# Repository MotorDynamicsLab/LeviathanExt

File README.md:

# Leviathan Extension Board

The Leviathan Extension Board is a plug and play PCB that expands the feature set of the original Leviathan controller board. It adds: 

- 2x Integrated TMC5160 stepper drivers. 
- 2x Fan ports with flyback protection, 12V/24V selectable voltage, and tachometer inputs. 
- 2x Thermistor ports with 2k2 ohm pullup resistors. 
- 1x Piezo Buzzer

## Electrical Specifications

| Parameter                 | Symbol             | Min | Typ | Max | Unit | Comments                                      |
| ------------------------- | ------------------ | --- | --- | --- | ---- | --------------------------------------------- |
| HV Stepper Supply Voltage | V<sub>HV</sub>     | 24  | 48  | 55  | V    | Supply voltage for the HV stepper drivers     |
| Fan Current               | I<sub>fan</sub>    |     |     | 0.5 | A    | Current rating per fan channel                |
| HV Stepper Current        | I<sub>hv_mot</sub> |     |     | 3   | A    | Current rating of each TMC5160 stepper driver |

## Creating a Custom Extension PCB

Did you ever want to create your own custom extension board? We have a [template KiCad project](https://github.com/MotorDynamicsLab/Leviathan-Ext-Template) to help get you started.

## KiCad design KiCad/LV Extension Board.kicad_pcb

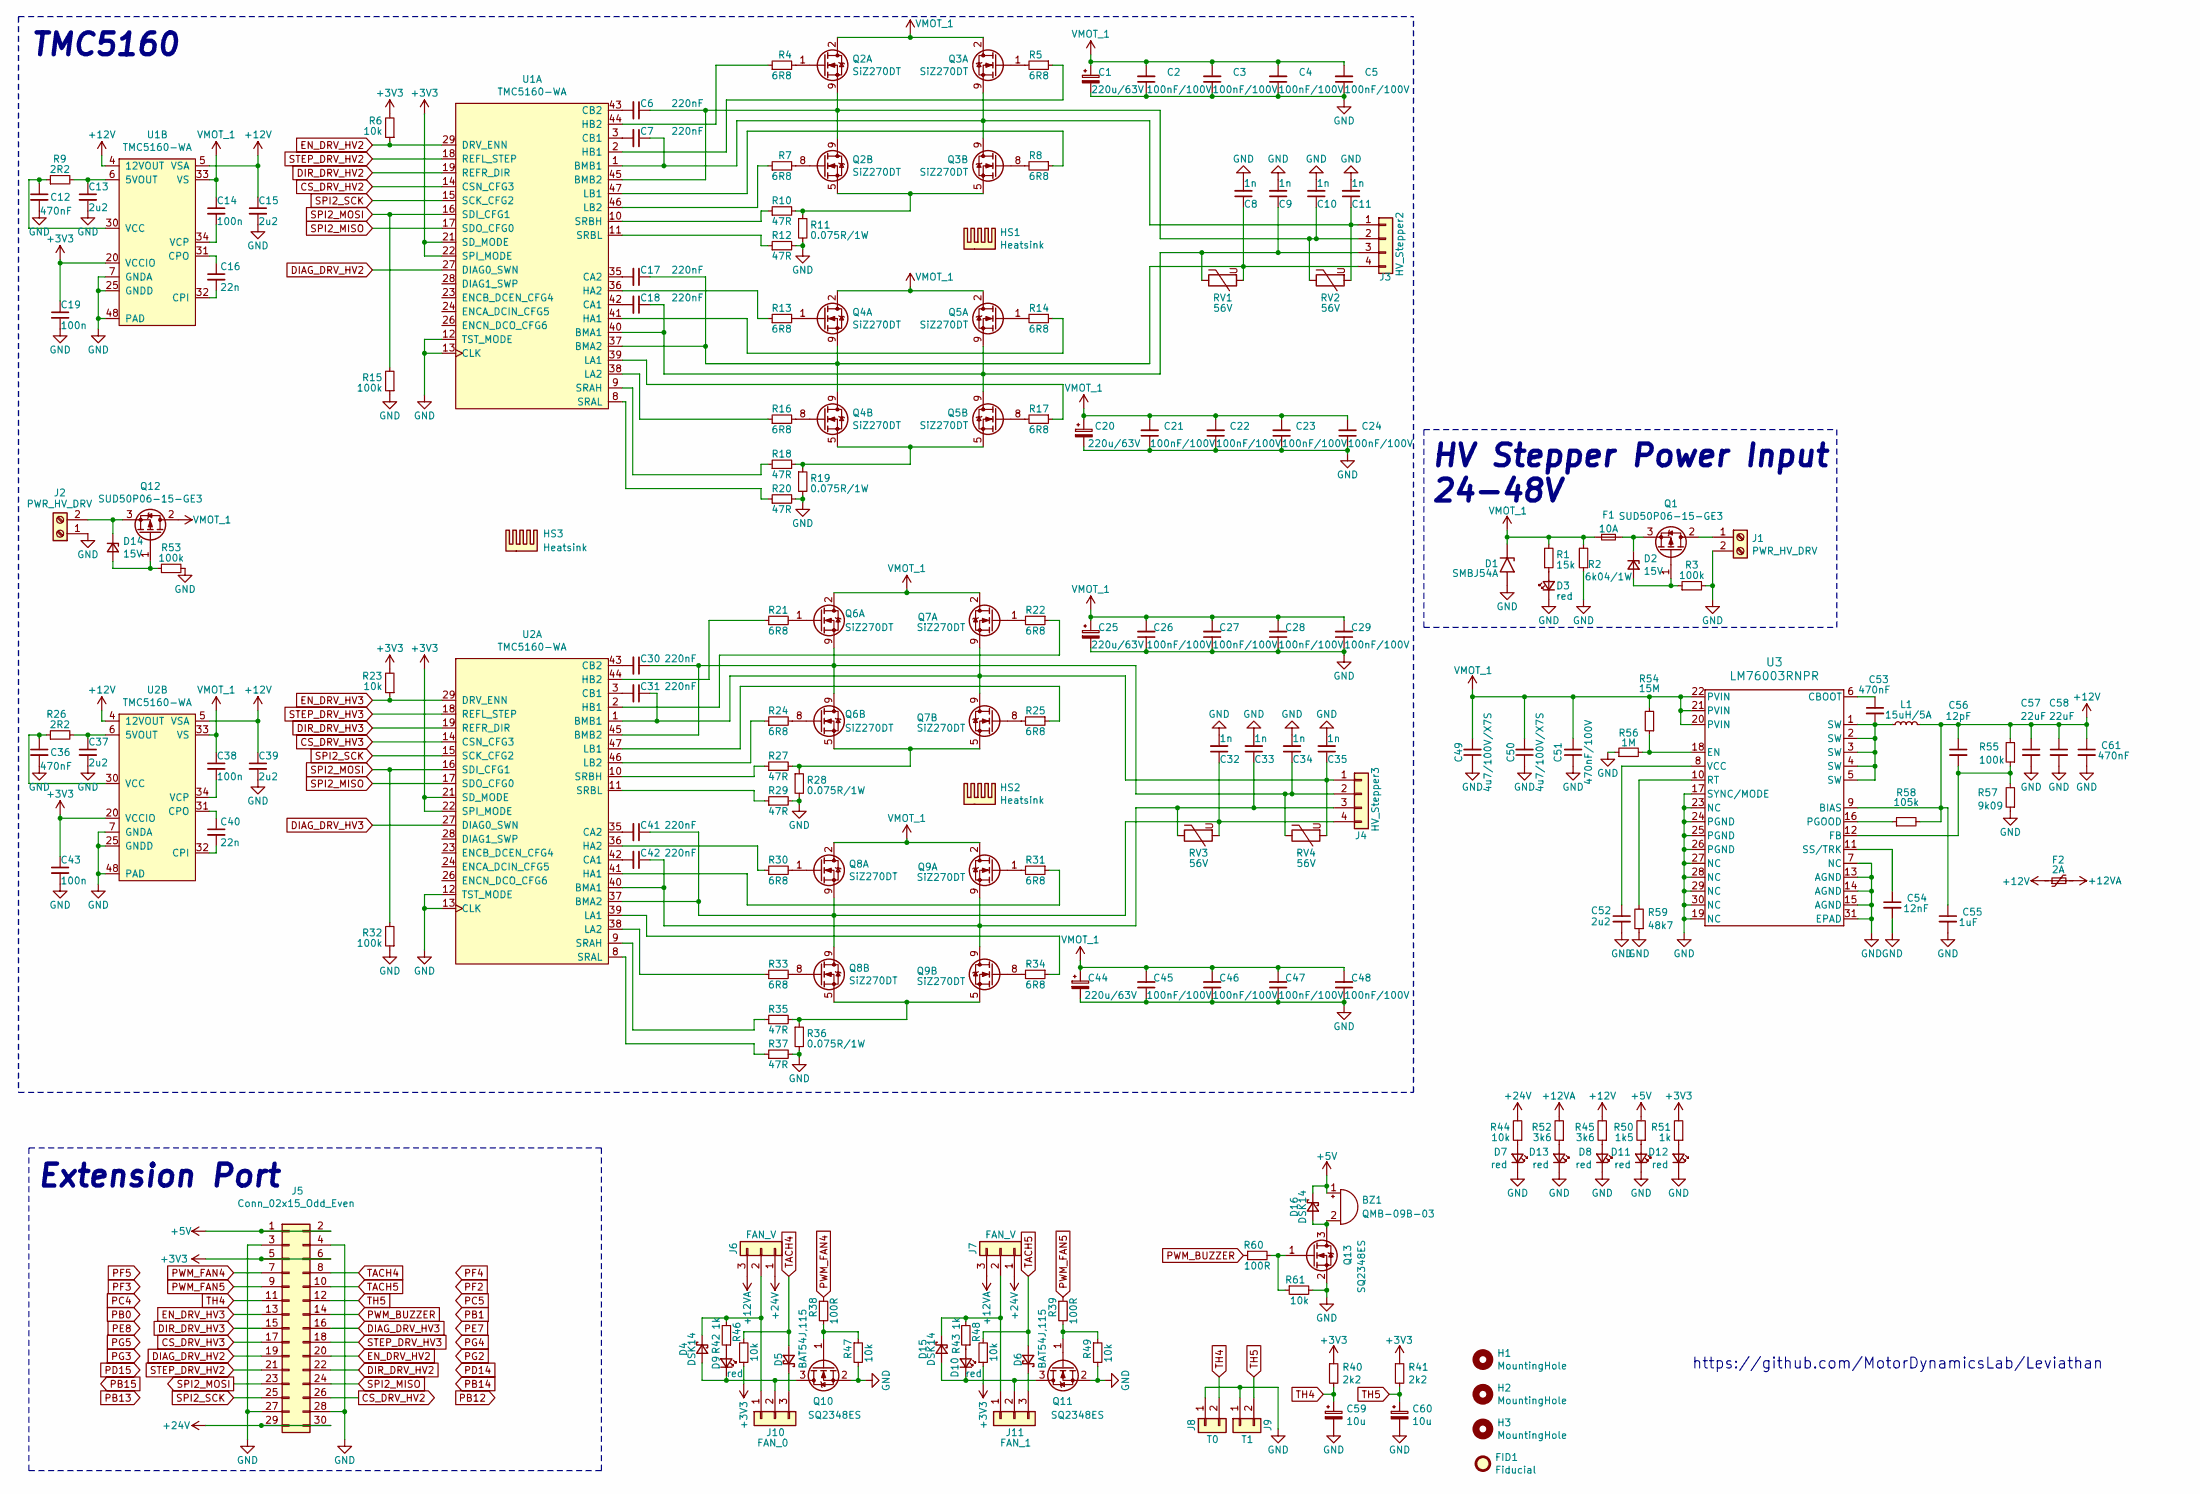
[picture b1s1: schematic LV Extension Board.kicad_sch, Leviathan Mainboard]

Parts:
BZ1: QMB-09B-03; MagneticBuzzer_PUI_AT-0927-TT-6-R; LCSC C96256
C1, C20, C25, C44: 220u/63V; CP_Radial_D10.0mm_P5.00mm; LCSC C442941
C2, C3, C4, C5, C21, C22, C23, C24, C26, C27, C28, C29, C45, C46, C47, C48: 100nF/100V; C_0603_1608Metric; LCSC C88219
C6, C7, C17, C18, C30, C31, C41, C42: 220nF; C_0603_1608Metric; LCSC C2174190
C8, C9, C10, C11, C32, C33, C34, C35: 1n; C_0603_1608Metric; MFG# 0603B102K101CT; LCSC C77438
C12, C36: 470nF; C_0402_1005Metric; LCSC C961501
C13, C15, C37, C39: 2u2; C_0603_1608Metric; LCSC C99228
C14: 100n; C_0603_1608Metric; LCSC# C116838
C16, C40: 22n; C_0603_1608Metric; LCSC C161234
C19, C43: 100n; C_0402_1005Metric; MFG# C83054; LCSC C83054
C38: 100n; C_0603_1608Metric; LCSC C116838
C49, C50: 4u7/100V/X7S; C_1206_3216Metric; LCSC C237304
C51: 470nF/100V; C_0805_2012Metric; LCSC C97926
C52: 2u2; C_0402_1005Metric; LCSC C2999759
C53, C61: 470nF; C_0402_1005Metric; LCSC C437527
C54: 12nF; C_0402_1005Metric; LCSC C113785
C55: 1uF; C_0402_1005Metric; LCSC C1518208
C56: 12pF; C_0402_1005Metric; LCSC C1547
C57, C58: 22uF; C_1206_3216Metric; LCSC C909845
C59, C60: 10u; CP_EIA-3216-18_Kemet-A; MFG# TC212A106M010B; LCSC# C124849
D1: SMBJ54A; D_SMB; LCSC C353352
D2, D14: 15V; D_SOD-123; LCSC C177014
D3, D7, D8, D9, D10, D11, D12, D13: red; LED_0603_1608Metric; LCSC C434419
D4, D15, D16: DSK14; D_SOD-123F; LCSC C37049
D5, D6: BAT54J,115; D_SOD-323_HandSoldering; LCSC C130415
F1: 10A; Fuseholder_Littelfuse_Nano2_154x; LCSC C206921
F2: 2A; Fuse_0805_2012Metric; LCSC C910824
FID1: Fiducial; Fiducial_1.5mm_Mask3mm
H1, H2, H3: MountingHole; MountingHole_3.2mm_M3_Pad_TopBottom
HS1, HS2: Heatsink; Heatsink_Fischer_ICK_PGA_20x20x10
HS3: Heatsink; M2_Heatsink_55x22x3
J1, J2: PWR_HV_DRV; TerminalBlock_Phoenix_MKDS-1,5-2_1x02_P5.00mm_Horizontal
J3: HV_Stepper2; JST_XH_B4B-XH-A_1x04_P2.50mm_Vertical; LCSC C566013
J4: HV_Stepper3; JST_XH_B4B-XH-A_1x04_P2.50mm_Vertical; LCSC C566013
J5: Conn_02x15_Odd_Even; PinHeader_2x15_P2.54mm_Horizontal
J6, J7: FAN_V; PinHeader_1x03_P2.54mm_Vertical; LCSC C429954
J8: T0; JST_XH_B2B-XH-A_1x02_P2.50mm_Vertical; LCSC C161869
J9: T1; JST_XH_B2B-XH-A_1x02_P2.50mm_Vertical; LCSC C161869
J10: FAN_0; JST_XH_B3B-XH-A_1x03_P2.50mm_Vertical; LCSC C565985
J11: FAN_1; JST_XH_B3B-XH-A_1x03_P2.50mm_Vertical; LCSC C565985
L1: 15uH/5A; L_Chilisin_BMRB00060650; LCSC C2847544
Q1, Q12: SUD50P06-15-GE3; TO-252-2; LCSC C141584
Q2, Q3, Q4, Q5: SiZ270DT; Vishay_PowerPair_3x3S; LCSC C17341509
Q6, Q7, Q8, Q9: SiZ270DT; Vishay_PowerPair_3x3S
Q10, Q11, Q13: SQ2348ES; SOT-23; LCSC C7463653
R1: 15k; R_0603_1608Metric; LCSC C73802
R2: 6k04/1W; R_2512_6332Metric; LCSC C421527
R3, R53: 100k; R_0603_1608Metric; LCSC C14675
R4, R5, R7, R8, R13, R14, R16, R17, R21, R22, R24, R25, R30, R31, R33, R34: 6R8; R_0402_1005Metric; LCSC C227211
R6, R23: 10k; R_0402_1005Metric; LCSC C384294
R9, R26: 2R2; R_0402_1005Metric; LCSC C327251
R10, R12, R18, R20, R27, R29, R35, R37: 47R; R_0402_1005Metric; LCSC C144756
R11, R19, R28, R36: 0.075R/1W; R_2512_6332Metric; LCSC C705611
R15, R32: 100k; R_0402_1005Metric; LCSC C132374
R38, R39, R60: 100R; R_0603_1608Metric; LCSC C327825
R40, R41: 2k2; R_0603_1608Metric; LCSC C445630
R42, R43, R51: 1k; R_0603_1608Metric; LCSC C14676
R44: 10k; R_0603_1608Metric; LCSC# C384294
R45, R52: 3k6; R_0603_1608Metric; LCSC C103578
R46, R47, R48, R49, R61: 10k; R_0603_1608Metric; LCSC C384294
R50: 1k5; R_0603_1608Metric; LCSC C22843
R54: 15M; R_0402_1005Metric; LCSC C7422144
R55: 100k; R_0402_1005Metric; LCSC C60491
R56: 1M; R_0402_1005Metric; LCSC C26083
R57: 9k09; R_0402_1005Metric; LCSC C11549
R58: 105k; R_0402_1005Metric; LCSC C171671
R59: 48k7; R_0402_1005Metric; LCSC C103068
RV1, RV2, RV3, RV4: 56V; R_1206_3216Metric; LCSC C2935553
U1, U2: TMC5160-WA; QFN-56-1EP_8x8mm_P0.5mm_EP6.25x6.25mm_ThermalVias_TMC; LCSC C1161714
U3: LM76003RNPR; Texas_RNP30; LCSC C470958

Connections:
+3V3: C19.1, C43.1, J5.5, J5.6, R6.2, R23.2, R40.1, R41.1, R46.1, R48.1, R51.2, U1.20 (VCCIO), U1.21 (SD_MODE), U1.22 (SPI_MODE), U2.20 (VCCIO), U2.21 (SD_MODE), U2.22 (SPI_MODE)
+5V: BZ1.1 (+), D16.1 (K), J5.1, J5.2, R50.2
+12V: C15.1, C39.1, C55.1, C56.1, C57.1, C58.1, C61.1, F2.1, L1.2, R45.2, R55.2, R58.2, U1.4 (12VOUT), U1.5 (VSA), U2.4 (12VOUT), U2.5 (VSA), U3.9 (BIAS)
+12VA: F2.2, J6.3, J7.3, R52.2
+24V: J5.29, J5.30, J6.1, J7.1, R44.2
CS_DRV_HV2: J5.26, U1.14 (CSN_CFG3)
CS_DRV_HV3: J5.17, U2.14 (CSN_CFG3)
DIAG_DRV_HV2: J5.19, U1.27 (DIAG0_SWN)
DIAG_DRV_HV3: J5.16, U2.27 (DIAG0_SWN)
DIR_DRV_HV2: J5.22, U1.19 (REFR_DIR)
DIR_DRV_HV3: J5.15, U2.19 (REFR_DIR)
EN_DRV_HV2: J5.20, R6.1, U1.29 (DRV_ENN)
EN_DRV_HV3: J5.13, R23.1, U2.29 (DRV_ENN)
GND: C1.2, C2.1, C3.1, C4.1, C5.1, C8.2, C9.2, C10.2, C11.2, C12.2, C13.2, C15.2, C19.2, C20.2, C21.1, C22.1, C23.1, C24.1, C25.2, C26.1, C27.1, C28.1, C29.1, C32.2, C33.2, C34.2, C35.2, C36.2, C37.2, C39.2, C43.2, C44.2, C45.1, C46.1, C47.1, C48.1, C49.1, C50.1, C51.1, C52.2, C54.2, C55.2, C57.2, C58.2, C59.2, C60.2, C61.2, D1.2 (A2), D3.1 (K), D7.1 (K), D8.1 (K), D11.1 (K), D12.1 (K), D13.1 (K), J1.2, J2.1, J5.3, J5.4, J5.27, J5.28, J8.1, J9.1, Q10.2 (S), Q11.2 (S), Q13.2 (S), R2.1, R3.2, R11.2, R12.2, R15.1, R19.2, R20.2, R28.2, R29.2, R32.1, R36.2, R37.2, R47.2, R49.2, R53.2, R56.1, R57.1, R59.1, R61.2, U1.7 (GNDA), U1.12 (TST_MODE), U1.13 (CLK), U1.25 (GNDD), U1.48 (PAD), U2.7 (GNDA), U2.12 (TST_MODE), U2.13 (CLK), U2.25 (GNDD), U2.48 (PAD), U3.7 (NC), U3.13 (AGND), U3.14 (AGND), U3.15 (AGND), U3.17 (SYNC/MODE), U3.19 (NC), U3.23 (NC), U3.24 (PGND), U3.25 (PGND), U3.26 (PGND), U3.27 (NC), U3.28 (NC), U3.29 (NC), U3.30 (NC), U3.31 (EPAD)
unnamed: BZ1.2 (-), D16.2 (A), Q13.3 (D)
unnamed: C53.2, L1.1, U3.1 (SW), U3.2 (SW), U3.3 (SW), U3.4 (SW), U3.5 (SW)
unnamed: D2.2 (A), Q1.1 (G), R3.1
unnamed: D2.1 (K), F1.2, Q1.3 (S)
unnamed: D3.2 (A), R1.1
unnamed: D4.2 (A), D9.1 (K), J10.2, Q10.3 (D)
unnamed: D4.1 (K), J6.2, J10.1, R42.2
unnamed: D5.1 (K), J10.3
unnamed: D6.1 (K), J11.3
unnamed: D7.2 (A), R44.1
unnamed: D8.2 (A), R45.1
unnamed: D9.2 (A), R42.1
unnamed: D10.2 (A), R43.1
unnamed: D10.1 (K), D15.2 (A), J11.2, Q11.3 (D)
unnamed: D11.2 (A), R50.1
unnamed: D12.2 (A), R51.1
unnamed: D13.2 (A), R52.1
unnamed: D14.2 (A), Q12.1 (G), R53.1
unnamed: D14.1 (K), J2.2, Q12.3 (S)
unnamed: D15.1 (K), J7.2, J11.1, R43.2
unnamed: J1.1, Q1.2 (D)
unnamed: C7.1, C11.1, J3.1, Q3.9 (S), RV2.2, U1.1 (BMB1)
unnamed: C6.1, C10.1, J3.2, Q2.9 (S), RV2.1, U1.45 (BMB2)
unnamed: C9.1, C18.1, J3.3, Q5.9 (S), RV1.1, U1.40 (BMA1)
unnamed: C8.1, C17.1, J3.4, Q4.9 (S), RV1.2, U1.37 (BMA2)
unnamed: C31.1, C35.1, J4.1, Q7.9 (S), RV4.2, U2.1 (BMB1)
unnamed: C30.1, C34.1, J4.2, Q6.9 (S), RV4.1, U2.45 (BMB2)
unnamed: C33.1, C42.1, J4.3, Q9.9 (S), RV3.1, U2.40 (BMA1)
unnamed: C32.1, C41.1, J4.4, Q8.9 (S), RV3.2, U2.37 (BMA2)
unnamed: Q2.1 (G), R4.2
unnamed: Q2.8 (G), R7.2
unnamed: Q2.5 (S), Q3.5 (S), R10.2, R11.1
unnamed: Q3.1 (G), R5.2
unnamed: Q3.8 (G), R8.2
unnamed: Q4.1 (G), R13.2
unnamed: Q4.8 (G), R16.2
unnamed: Q4.5 (S), Q5.5 (S), R18.2, R19.1
unnamed: Q5.1 (G), R14.2
unnamed: Q5.8 (G), R17.2
unnamed: Q6.1 (G), R21.2
unnamed: Q6.8 (G), R24.2
unnamed: Q6.5 (S), Q7.5 (S), R27.2, R28.1
unnamed: Q7.1 (G), R22.2
unnamed: Q7.8 (G), R25.2
unnamed: Q8.1 (G), R30.2
unnamed: Q8.8 (G), R33.2
unnamed: Q8.5 (S), Q9.5 (S), R35.2, R36.1
unnamed: Q9.1 (G), R31.2
unnamed: Q9.8 (G), R34.2
unnamed: Q10.1 (G), R38.2, R47.1
unnamed: Q11.1 (G), R39.2, R49.1
unnamed: Q13.1 (G), R60.2, R61.1
unnamed: C18.2, U1.42 (CA1)
unnamed: C17.2, U1.35 (CA2)
unnamed: C7.2, U1.3 (CB1)
unnamed: C6.2, U1.43 (CB2)
unnamed: R14.1, U1.41 (HA1)
unnamed: R13.1, U1.36 (HA2)
unnamed: R5.1, U1.2 (HB1)
unnamed: R4.1, U1.44 (HB2)
unnamed: R17.1, U1.39 (LA1)
unnamed: R16.1, U1.38 (LA2)
unnamed: R8.1, U1.47 (LB1)
unnamed: R7.1, U1.46 (LB2)
unnamed: R18.1, U1.9 (SRAH)
unnamed: R20.1, U1.8 (SRAL)
unnamed: R10.1, U1.10 (SRBH)
unnamed: R12.1, U1.11 (SRBL)
unnamed: C13.1, R9.2, U1.6 (5VOUT)
unnamed: C16.2, U1.32 (CPI)
unnamed: C16.1, U1.31 (CPO)
unnamed: C12.1, R9.1, U1.30 (VCC)
unnamed: C14.2, U1.34 (VCP)
unnamed: C42.2, U2.42 (CA1)
unnamed: C41.2, U2.35 (CA2)
unnamed: C31.2, U2.3 (CB1)
unnamed: C30.2, U2.43 (CB2)
unnamed: R31.1, U2.41 (HA1)
unnamed: R30.1, U2.36 (HA2)
unnamed: R22.1, U2.2 (HB1)
unnamed: R21.1, U2.44 (HB2)
unnamed: R34.1, U2.39 (LA1)
unnamed: R33.1, U2.38 (LA2)
unnamed: R25.1, U2.47 (LB1)
unnamed: R24.1, U2.46 (LB2)
unnamed: R35.1, U2.9 (SRAH)
unnamed: R37.1, U2.8 (SRAL)
unnamed: R27.1, U2.10 (SRBH)
unnamed: R29.1, U2.11 (SRBL)
unnamed: C37.1, R26.2, U2.6 (5VOUT)
unnamed: C40.2, U2.32 (CPI)
unnamed: C40.1, U2.31 (CPO)
unnamed: C36.1, R26.1, U2.30 (VCC)
unnamed: C38.2, U2.34 (VCP)
unnamed: C53.1, U3.6 (CBOOT)
unnamed: R54.1, R56.2, U3.18 (EN)
unnamed: C56.2, R55.1, R57.2, U3.12 (FB)
unnamed: R58.1, U3.16 (PGOOD)
unnamed: R59.2, U3.10 (RT)
unnamed: C54.1, U3.11 (SS/TRK)
unnamed: C52.1, U3.8 (VCC)
PWM_BUZZER: J5.14, R60.1
PWM_FAN4: J5.7, R38.1
PWM_FAN5: J5.9, R39.1
SPI2_MISO: J5.24, U1.17 (SDO_CFG0), U2.17 (SDO_CFG0)
SPI2_MOSI: J5.23, R15.2, R32.2, U1.16 (SDI_CFG1), U2.16 (SDI_CFG1)
SPI2_SCK: J5.25, U1.15 (SCK_CFG2), U2.15 (SCK_CFG2)
STEP_DRV_HV2: J5.21, U1.18 (REFL_STEP)
STEP_DRV_HV3: J5.18, U2.18 (REFL_STEP)
TACH4: D5.2 (A), J5.8, R46.2
TACH5: D6.2 (A), J5.10, R48.2
TH4: C59.1, J5.11, J8.2, R40.2
TH5: C60.1, J5.12, J9.2, R41.2
VMOT_1: C1.1, C2.2, C3.2, C4.2, C5.2, C14.1, C20.1, C21.2, C22.2, C23.2, C24.2, C25.1, C26.2, C27.2, C28.2, C29.2, C38.1, C44.1, C45.2, C46.2, C47.2, C48.2, C49.2, C50.2, C51.2, D1.1 (A1), F1.1, Q2.2 (D), Q3.2 (D), Q4.2 (D), Q5.2 (D), Q6.2 (D), Q7.2 (D), Q8.2 (D), Q9.2 (D), Q12.2 (D), R1.2, R2.2, R54.2, U1.33 (VS), U2.33 (VS), U3.20 (PVIN), U3.21 (PVIN), U3.22 (PVIN)

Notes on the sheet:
Extension Port
HV Stepper Power Input 24-48V
https://github.com/MotorDynamicsLab/Leviathan
TMC5160

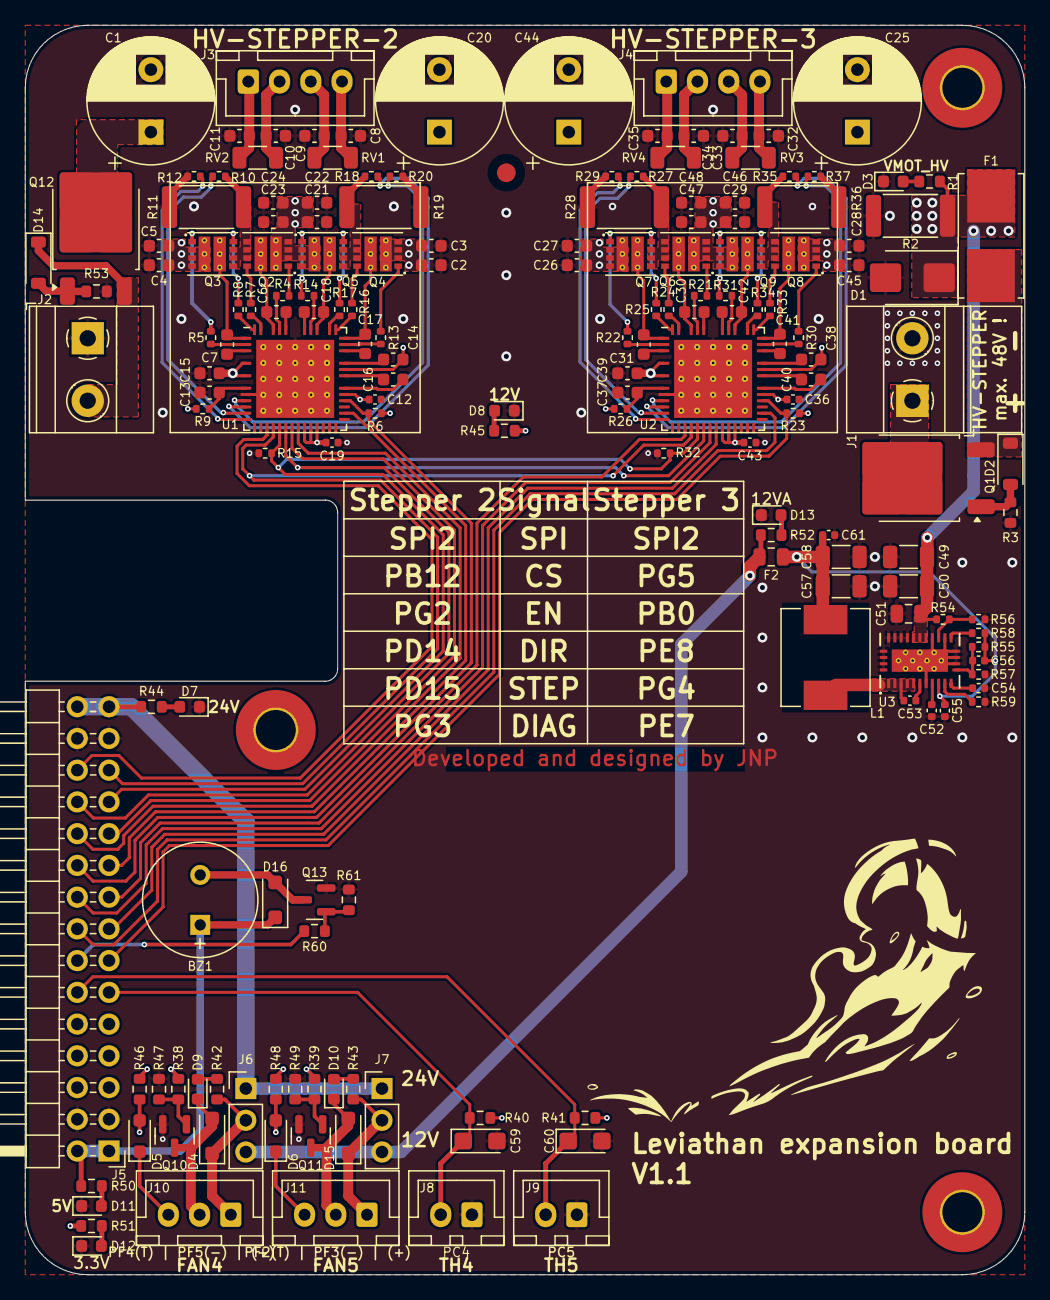
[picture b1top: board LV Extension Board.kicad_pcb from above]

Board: 4 copper layers, 80.0 x 100.0 mm, 180 parts (1 on the bottom side), 128 nets.

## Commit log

2025-05-06 add README.md
2025-05-06 add printed bracket files as well as photo images
2025-05-06 resize product_img_web.jpg
2025-05-06 add schematics
2025-05-06 add 3D model
2025-05-06 add gitignore
2025-05-06 add KiCAD source
2025-05-07 add klipper config
2025-05-07 add KiCad/PRODUCTION directory to gitignore
2025-05-12 add link to template project
2025-05-21 update buzzer config from normal output_pin to pwm_cycle_time
2025-05-29 added product_image.jpg
2025-05-29 resize
2025-05-29 updated image
